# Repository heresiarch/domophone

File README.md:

This is an example ESP8266 project

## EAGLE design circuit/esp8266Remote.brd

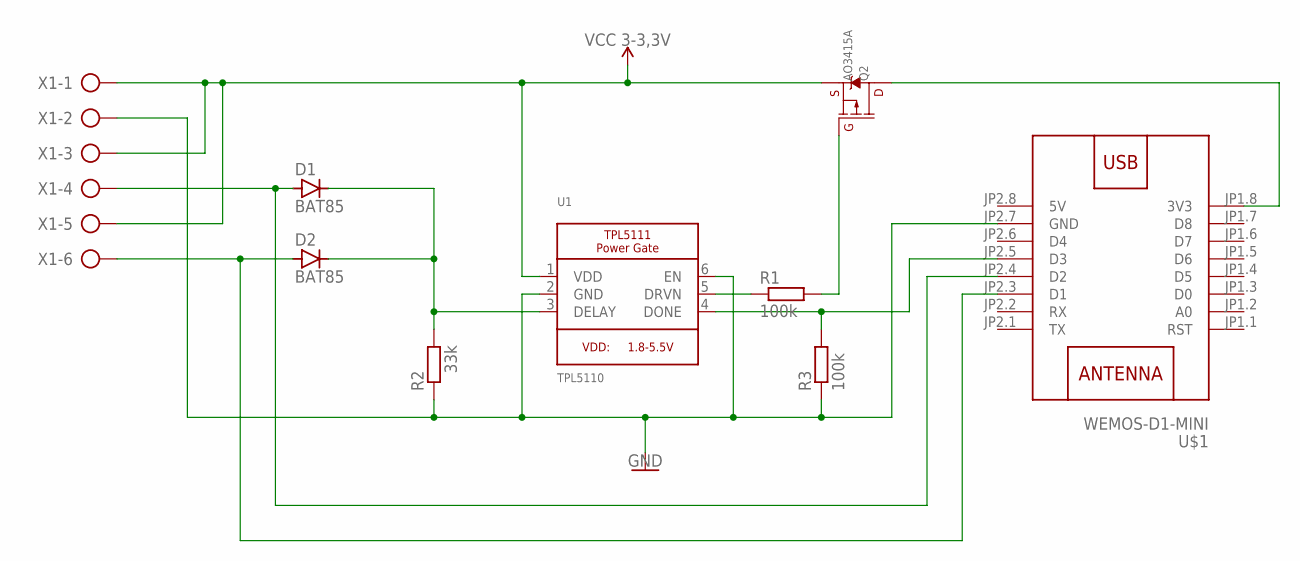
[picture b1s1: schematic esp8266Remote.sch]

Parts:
D1, D2: BAT85; D-5
Q2: AO3415A; HDRV3W64P254_1X3_1016X400X838B
R1: 100k; 0207/12
R2: 33k; 0204/5
R3: 100k; 0204/5
U1: TPL5110; DIP762W53P254L866H300Q6B
U$1: WEMOS-D1-MINI
X1: AK500/6

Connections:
5V: U$1.JP2.8 (5V)
GND: R2.1, R3.1, U1.2 (GND), U1.6 (EN), U$1.JP2.7 (GND), X1.2
unnamed: D2.A, U$1.JP2.3 (D1), X1.6
unnamed: Q2.2 (D), U$1.JP1.8 (3V3)
unnamed: R1.1, U1.5 (DRVN)
unnamed: Q2.3 (G), R1.2
unnamed: D1.A, U$1.JP2.4 (D2), X1.4
unnamed: R3.2, U1.4 (DONE), U$1.JP2.5 (D3)
unnamed: D1.C, D2.C, R2.2, U1.3 (DELAY)
VCC: Q2.1 (S), U1.1 (VDD), X1.1, X1.3, X1.5

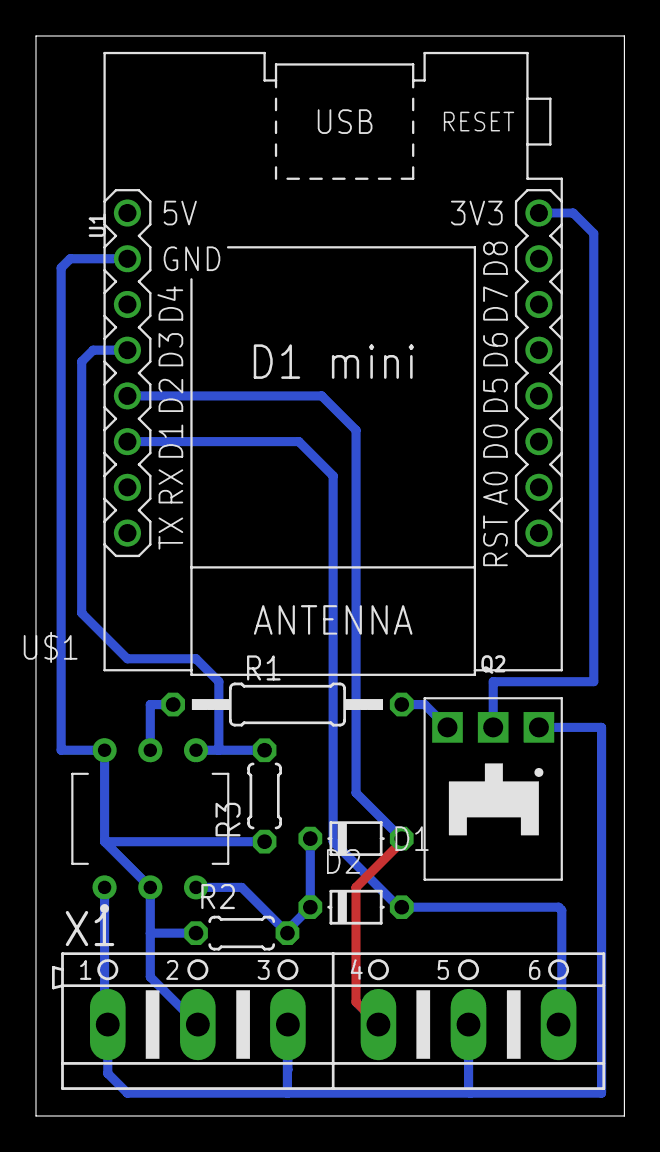
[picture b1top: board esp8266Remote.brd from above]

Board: 2 copper layers, 32.7 x 60.0 mm, 9 parts (0 on the bottom side), 9 nets.

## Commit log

2019-12-31 first
2019-12-31 reset
2019-12-31 clean
2019-12-31 improved button and reset handling
2020-01-12 first board layout
2020-02-04 latest

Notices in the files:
parts and their libraries:
diy-modules: Released under the Creative Commons Attribution 4.0 International License: http://creativecommons.org/licenses/by/4.0
SparkFun-PowerSymbols: Licensing: Creative Commons ShareAlike 4.0 International - https://creativecommons.org/licenses/by-sa/4.0
